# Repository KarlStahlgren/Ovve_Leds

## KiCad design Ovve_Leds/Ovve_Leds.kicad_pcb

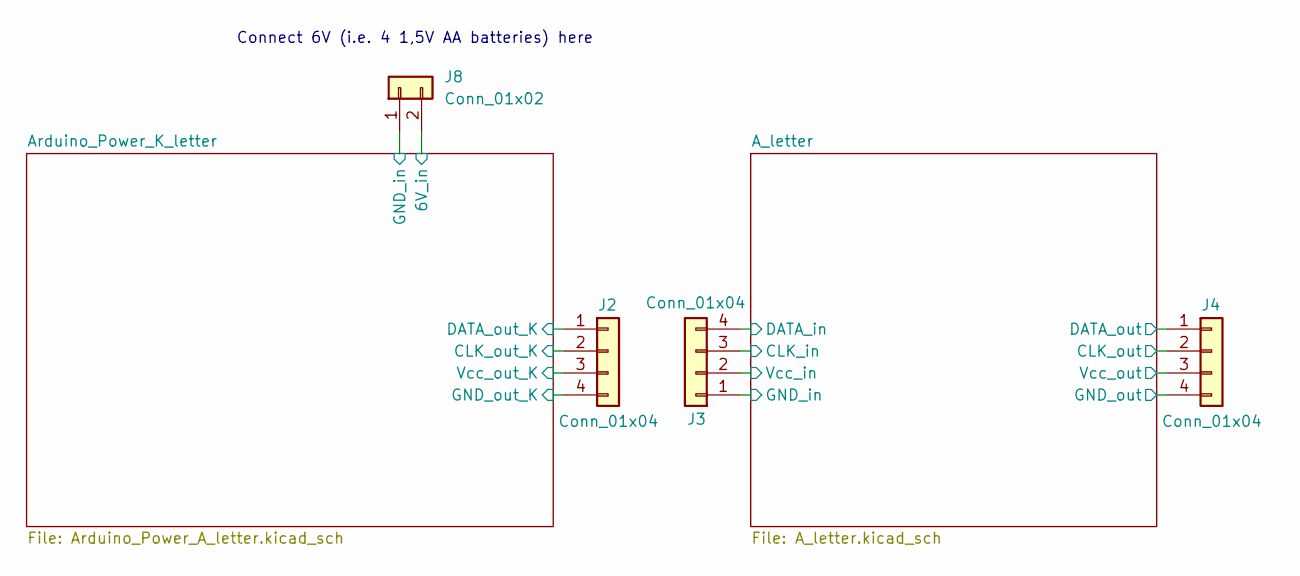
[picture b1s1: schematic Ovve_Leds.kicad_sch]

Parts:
J2, J3, J4: Conn_01x04; PinHeader_1x04_P2.54mm_Horizontal
J8: Conn_01x02; PinHeader_1x02_P2.54mm_Horizontal

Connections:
+5V: J2.3, J3.2, J4.3; also elsewhere on the board
/A_letter/CLK: J3.3, J4.2; also elsewhere on the board
/A_letter/DATA: J3.4; also elsewhere on the board
/A_letter/LED5: J4.1; also elsewhere on the board
/Arduino_Power_K_letter/6V_in: J8.2; also elsewhere on the board
/Arduino_Power_K_letter/CLK: J2.2; also elsewhere on the board
/Arduino_Power_K_letter/DATA: J2.1; also elsewhere on the board
GND: J2.4, J3.1, J4.4, J8.1; also elsewhere on the board

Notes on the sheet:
Connect 6V (i.e. 4 1,5V AA batteries) here

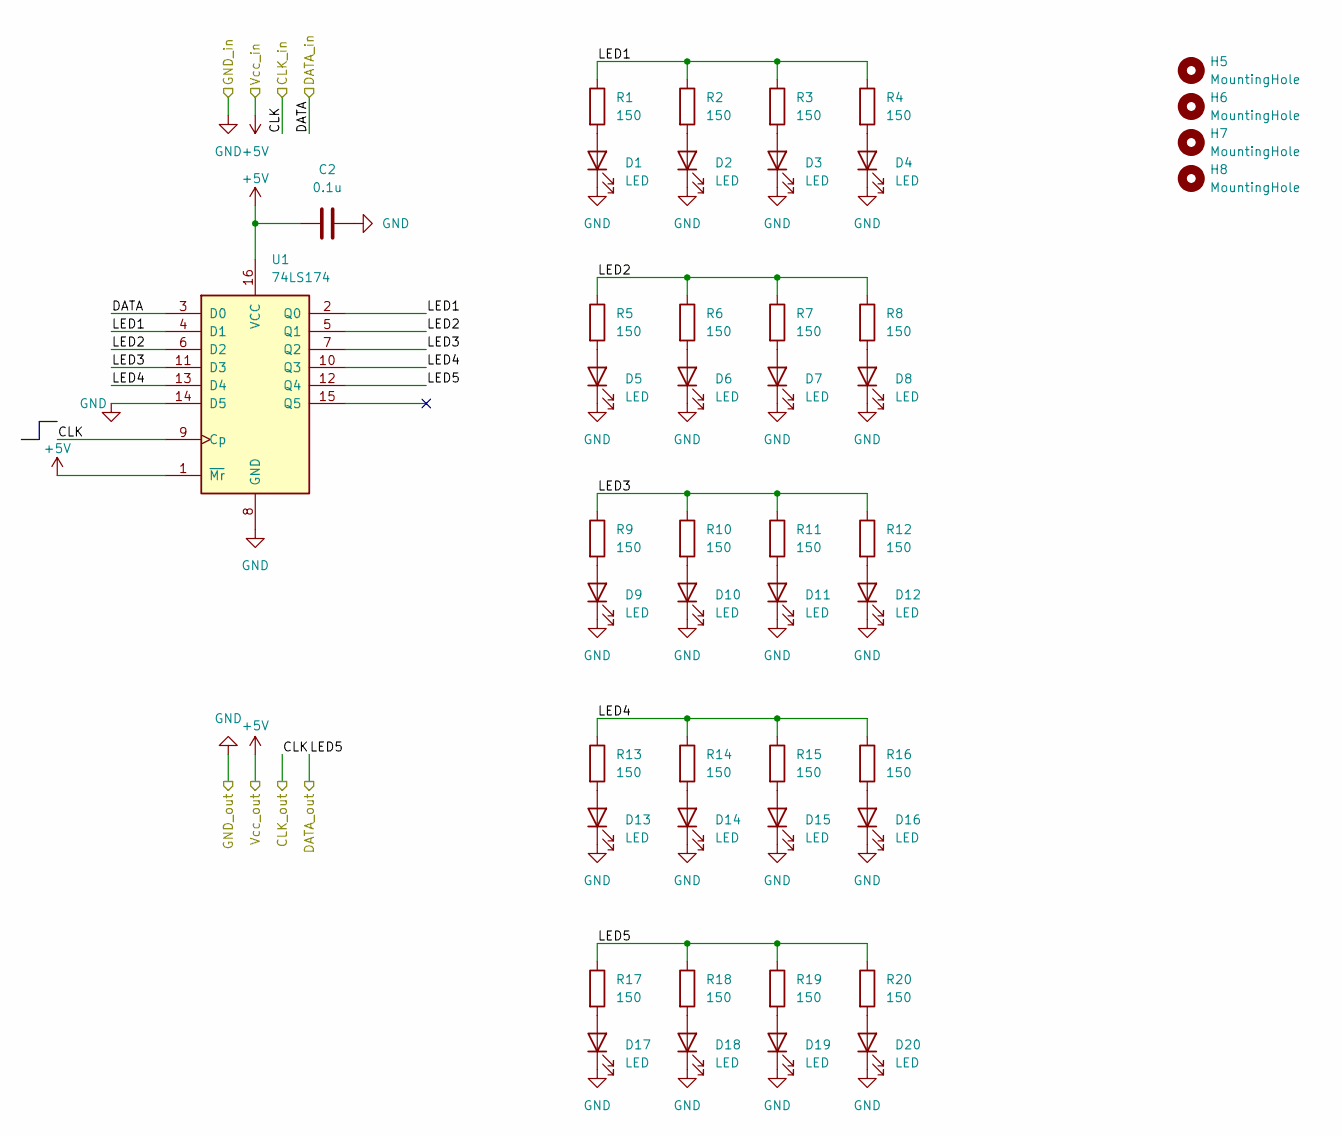
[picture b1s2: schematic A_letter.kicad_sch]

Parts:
C2: 0.1u; C_0603_1608Metric
D1, D2, D3, D4, D5, D6, D7, D8, D9, D10, D11, D12, D13, D14, D15, D16, D17, D18, D19, D20: LED; LED_D5.0mm
H5, H6, H7, H8: MountingHole; MountingHole_5.3mm_M5_DIN965_Pad
R1, R2, R3, R4, R5, R6, R7, R8, R9, R10, R11, R12, R13, R14, R15, R16, R17, R18, R19, R20: 150; R_0603_1608Metric
U1: 74LS174; DIP-16_W7.62mm

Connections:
+5V: C2.1, U1.1 (~Mr), U1.16 (VCC); also elsewhere on the board
/A_letter/CLK: U1.9 (Cp); also elsewhere on the board
/A_letter/DATA: U1.3 (D0); also elsewhere on the board
/A_letter/LED1: R1.1, R2.1, R3.1, R4.1, U1.2 (Q0), U1.4 (D1)
/A_letter/LED2: R5.1, R6.1, R7.1, R8.1, U1.5 (Q1), U1.6 (D2)
/A_letter/LED3: R9.1, R10.1, R11.1, R12.1, U1.7 (Q2), U1.11 (D3)
/A_letter/LED4: R13.1, R14.1, R15.1, R16.1, U1.10 (Q3), U1.13 (D4)
/A_letter/LED5: R17.1, R18.1, R19.1, R20.1, U1.12 (Q4); also elsewhere on the board
GND: C2.2, D1.1 (K), D2.1 (K), D3.1 (K), D4.1 (K), D5.1 (K), D6.1 (K), D7.1 (K), D8.1 (K), D9.1 (K), D10.1 (K), D11.1 (K), D12.1 (K), D13.1 (K), D14.1 (K), D15.1 (K), D16.1 (K), D17.1 (K), D18.1 (K), D19.1 (K), D20.1 (K), U1.8 (GND), U1.14 (D5); also elsewhere on the board
unnamed: D1.2 (A), R1.2
unnamed: D2.2 (A), R2.2
unnamed: D3.2 (A), R3.2
unnamed: D4.2 (A), R4.2
unnamed: D5.2 (A), R5.2
unnamed: D6.2 (A), R6.2
unnamed: D7.2 (A), R7.2
unnamed: D8.2 (A), R8.2
unnamed: D9.2 (A), R9.2
unnamed: D10.2 (A), R10.2
unnamed: D11.2 (A), R11.2
unnamed: D12.2 (A), R12.2
unnamed: D13.2 (A), R13.2
unnamed: D14.2 (A), R14.2
unnamed: D15.2 (A), R15.2
unnamed: D16.2 (A), R16.2
unnamed: D17.2 (A), R17.2
unnamed: D18.2 (A), R18.2
unnamed: D19.2 (A), R19.2
unnamed: D20.2 (A), R20.2

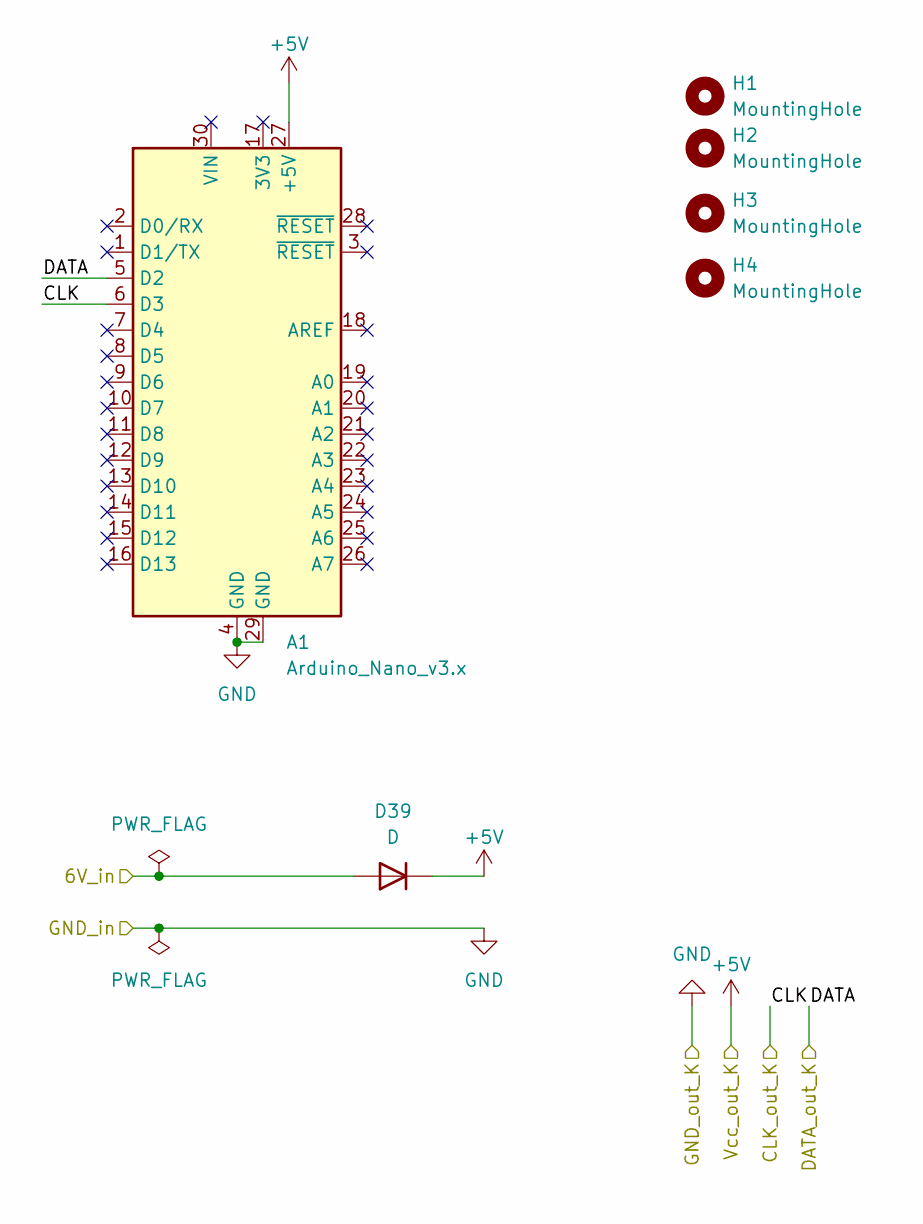
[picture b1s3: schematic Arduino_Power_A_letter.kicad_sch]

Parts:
A1: Arduino_Nano_v3.x; Arduino_Nano
D39: D; D_DO-201AD_P15.24mm_Horizontal
H1, H2, H3, H4: MountingHole; MountingHole_5.3mm_M5_DIN965_Pad
J1: Conn_01x04; PinHeader_1x04_P2.54mm_Horizontal

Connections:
+5V: A1.27 (+5V), D39.1 (K); also elsewhere on the board
/Arduino_Power_K_letter/6V_in: D39.2 (A); also elsewhere on the board
/Arduino_Power_K_letter/CLK: A1.6 (D3); also elsewhere on the board
/Arduino_Power_K_letter/DATA: A1.5 (D2); also elsewhere on the board
GND: A1.4 (GND), A1.29 (GND); also elsewhere on the board

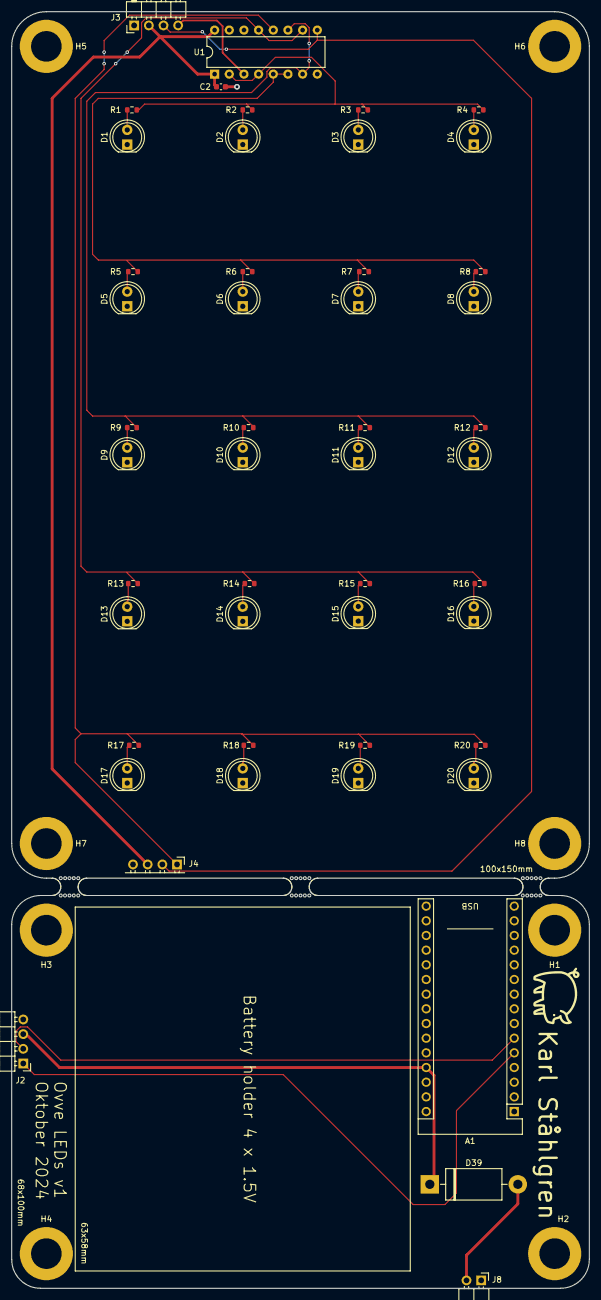
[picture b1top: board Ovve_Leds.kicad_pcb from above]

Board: 2 copper layers, 100.0 x 221.0 mm, 59 parts (0 on the bottom side), 32 nets.

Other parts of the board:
mouse-bite-3mm-slot, mouse-bite-3mm-slot#2, mouse-bite-3mm-slot#3: VAL**; mouse-bite-3mm-slot

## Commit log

2024-06-10 Added hierarchical sheets for letters
2024-06-11 Finished preliminary schematics
2024-06-11 Added decoupling capacitors and assigned footprints
2024-06-12 updated footprint of connector
2024-06-12 Updated flip-flops
2024-06-13 Component layout on PCB
2024-06-13 Removed annoying lck files and updated gitignore
2024-06-13 Finished routing K and A
2024-06-18 Finished routing
2024-09-25 Started work on new design with only one letter
2024-09-25 Added more LEDs to make letters more visible since there will be no silkscreen
2024-09-28 Changed to 5x4
2024-09-28 problem with CLK not connecting
2024-10-04 Preliminarily finished with routing letter
2024-10-04 Before adding mouse bites, routing finished
2024-10-04 added mouse bites
